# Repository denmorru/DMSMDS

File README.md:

# DMSMDS
(Wemos) D1 mini stepper motor driver shield <br> (for Pololu socket drivers with 8pin*2row connector).
<br>
12V power in, both for 5.0V stabilizer and motor load.
<br>

Bill of materials:<br>
1. PCB (1)<br>
2. Header female 8x1 pin (2)<br>
3. Header male 8x1 pin (2)<br>
4. Header male 6x1 pin (1)<br>
5. Capacitor 0.1mF (1)<br>
6. Capacitor 22uF (1)<br>
7. Resistor 4.7K (2)<br>
8. Voltage regulator AMS1117-5.0V 1A SOT-223 (1)<br>
9. Header male 3x2 pin (1)<br>

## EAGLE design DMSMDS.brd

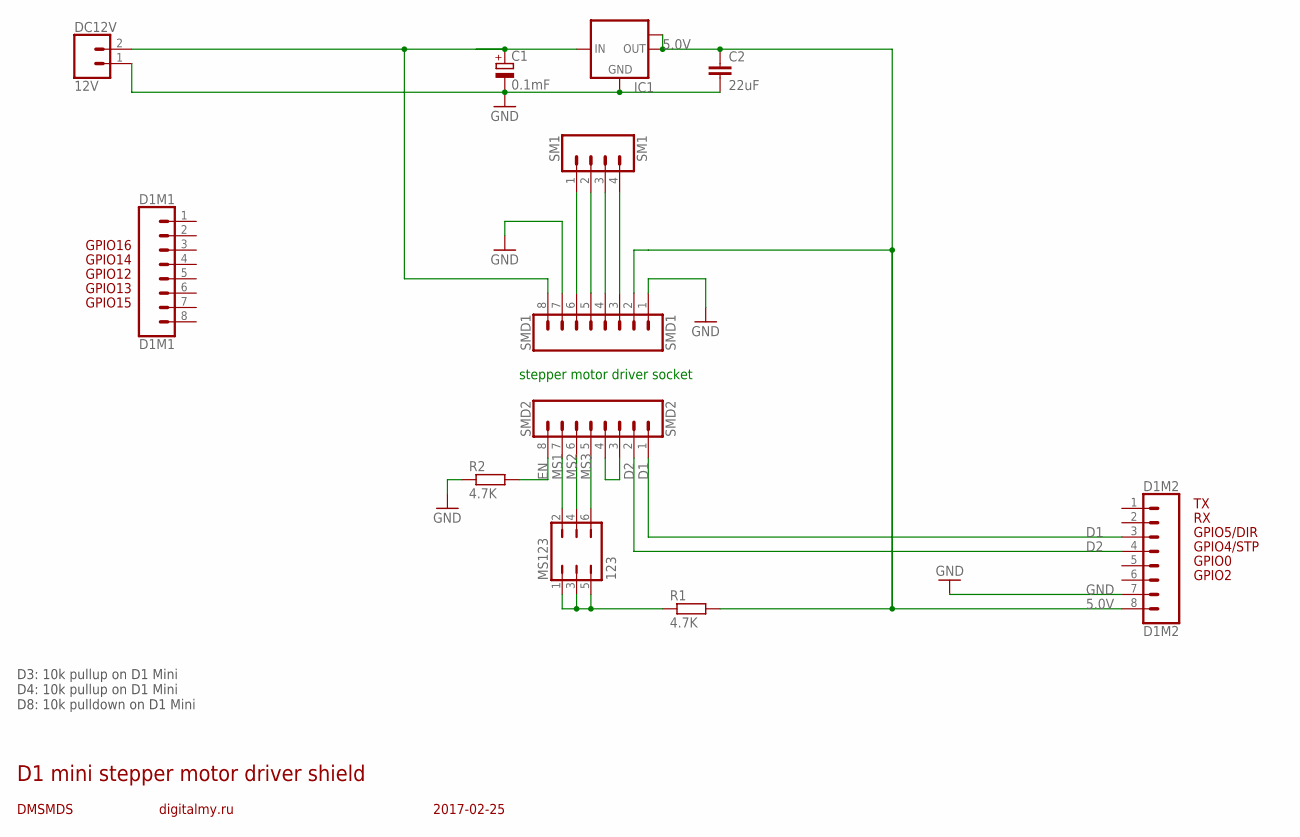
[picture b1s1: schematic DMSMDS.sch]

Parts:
C1: 0.1mF; E5-8,5
C2: 22uF; C1206
D1M1: D1M1; 1X08
D1M2: D1M2; 1X08
DC12V: 12V; 1X02
IC1: LM1117MPX-5.0; SOT223
MS123: 123; JP3Q
R1, R2: 4.7K; R0402
SM1: SM1; 1X04
SMD1: SMD1; 1X08_NO_SILK
SMD2: SMD2; 1X08_NO_SILK

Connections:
5.0V: C2.1, D1M2.8, IC1.2 (OUT), IC1.TAB (OUT1), R1.2, SMD1.2
12V: C1.+, DC12V.2, IC1.3 (IN), SMD1.8
D1: D1M2.3, SMD2.1
D2: D1M2.4, SMD2.2
EN: R2.2, SMD2.8
GND: C1.-, C2.2, D1M2.7, DC12V.1, IC1.1 (GND), R2.1, SMD1.1, SMD1.7
MS1: MS123.2, SMD2.7
MS2: MS123.4, SMD2.6
MS3: MS123.6, SMD2.5
MSP: MS123.1, MS123.3, MS123.5, R1.1
unnamed: SM1.1, SMD1.6
unnamed: SM1.2, SMD1.5
unnamed: SM1.3, SMD1.4
unnamed: SM1.4, SMD1.3
unnamed: SMD2.3, SMD2.4

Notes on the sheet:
GPIO2
GPIO0
GPIO12
GPIO4/STP
GPIO5/DIR
GPIO13
GPIO14
GPIO15
GPIO16
DMSMDS
D1 mini stepper motor driver shield
2017-02-25
digitalmy.ru
D3: 10k pullup on D1 Mini D4: 10k pullup on D1 Mini D8: 10k pulldown on D1 Mini
stepper motor driver socket

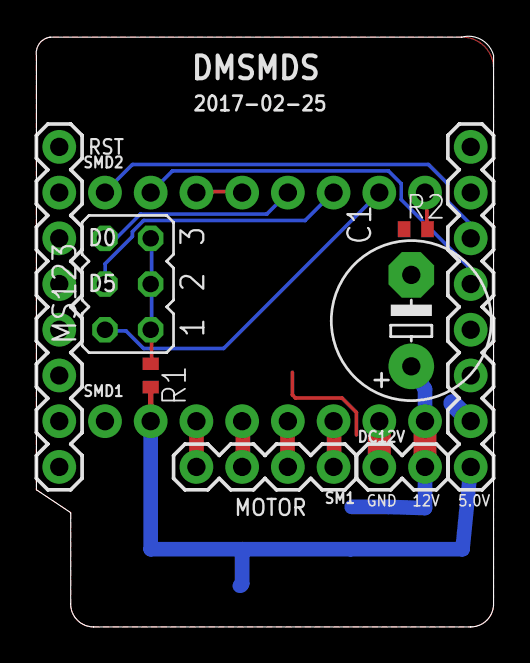
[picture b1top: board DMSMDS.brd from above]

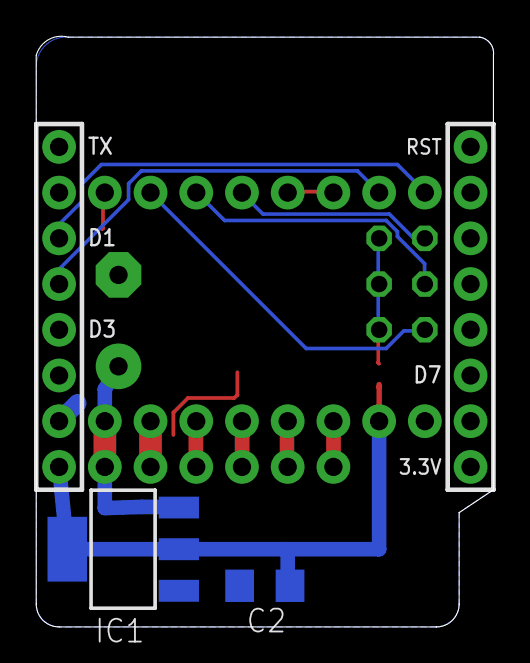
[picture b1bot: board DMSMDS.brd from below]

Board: 2 copper layers, 25.4 x 32.8 mm, 12 parts (2 on the bottom side), 15 nets.

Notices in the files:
parts and their libraries:
SparkFun-Connectors: Licensing: Creative Commons ShareAlike 4.0 International - https://creativecommons.org/licenses/by-sa/4.0
freetronics-original: Licensing: CC v3.0 Share-Alike You are welcome to use this library for commercial purposes.
